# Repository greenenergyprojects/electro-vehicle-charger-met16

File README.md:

# Electrovehicle IEC 62196 Typ 2 charger met-16

## Features:

* Charger Box for electro vehicle 230V/16A -> IEC 62196 Typ 2
* Charge current adjustable between 7A and 16A
* Controlled by Atmel Atmega328P microcontroller (Arduino nano)
* Optional: voltage and current measurement on board
* Optional: LCD connector (2x20 characters, 4 bit mode)

## Newest version ready to use

* [Branch v0.3](https://github.com/greenenergyprojects/electro-vehicle-charger-met16/tree/v0.3)
* PCB: [kicad/dist](kicad/dist)
* Software: [software/atmega328p_u1/ev-charge-control/released](software/atmega328p_u1/ev-charge-control/released)

See README.md files in subfolders for more information.

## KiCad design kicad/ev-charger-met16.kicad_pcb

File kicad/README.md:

# Electrovehicle IEC 62196 Typ 2 charger met-16

## Issues / Test results

Issues can be found in file [dist/README.md](dist/README.md).

## PCB / Kicad project

Design files can be found in the [same directory](./).

## Tapeout / Manufactering data

Manufactering data can be found in subdirectory [dist](dist).

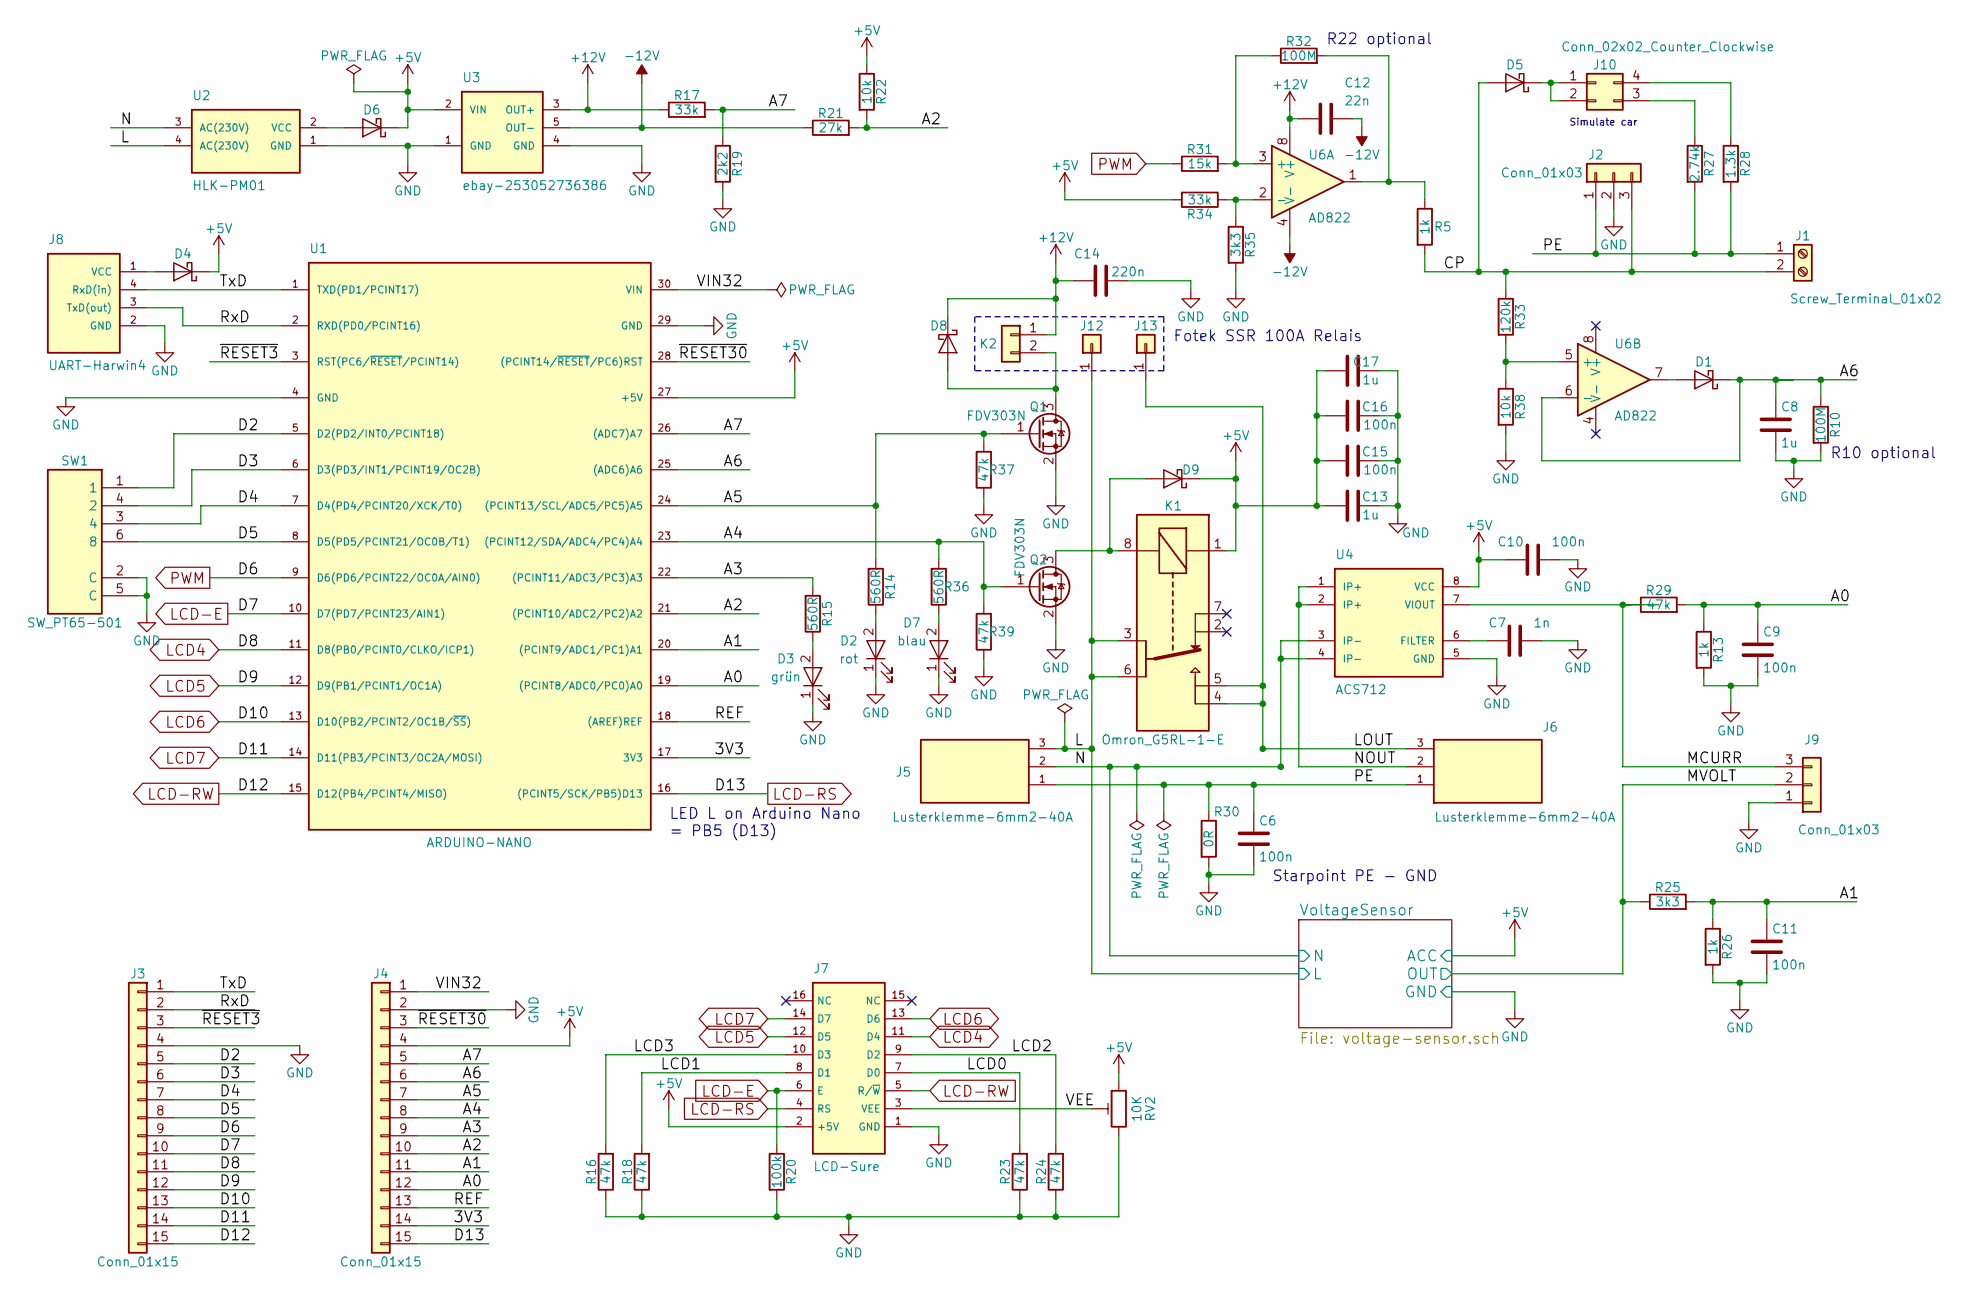
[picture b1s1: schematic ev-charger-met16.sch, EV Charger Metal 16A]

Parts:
C6, C9, C10, C11, C15, C16: 100n; C_1206_HandSoldering
C7: 1n; C_1206_HandSoldering
C8, C13, C17: 1u; C_1206_HandSoldering
C12: 22n; C_1206_HandSoldering
C14: 220n; C_1206_HandSoldering
D1, D4, D5, D8, D9: D_Schottky; D_SMA_Handsoldering
D2: rot; LED_PLCC-2
D3: grün; LED_PLCC-2
D6: D_Schottky; D_SMA-SMB_Universal_Handsoldering
D7: blau; LED_PLCC-2
J1: Screw_Terminal_01x02; Terminalblock-2x-5mm
J2, J9: Conn_01x03; Pin_Header_Straight_1x03_Pitch2.54mm
J3, J4: Conn_01x15; Pin_Header_Straight_1x15_Pitch2.54mm
J5: Lusterklemme-6mm2-40A; Lusterklemme-PA30P-6mm2-40A-x3-N
J6: Lusterklemme-6mm2-40A; Lusterklemme-PA30P-6mm2-40A-x3-S
J7: LCD-Sure; LCD-Sure-shifted-064
J8: UART-Harwin4; Harwin_LTek-Male_04x2.00mm_Straight_StrainRelief
J10: Conn_02x02_Counter_Clockwise; Pin_Header_Straight_2x02_Pitch2.54mm
J12, J13: Conn_01x01; Solder_via_5x5_forWire4mm2
K1: Omron_G5RL-1-E; Relay_DPDT_Panasonic_JW2
K2: Conn_01x02; Pin_Header_Straight_1x02_Pitch2.54mm
Q1, Q2: FDV303N; SOT-23_Handsoldering
R5, R13, R26: 1k; R_1206_HandSoldering
R10, R32: 100M; R_1206_HandSoldering
R14, R15, R36: 560R; R_1206_HandSoldering
R16, R18, R23, R24, R29, R37, R39: 47k; R_1206_HandSoldering
R17, R34: 33k; R_1206_HandSoldering
R19: 2k2; R_1206_HandSoldering
R20: 100k; R_1206_HandSoldering
R21: 27k; R_1206_HandSoldering
R22, R38: 10k; R_1206_HandSoldering
R25, R35: 3k3; R_1206_HandSoldering
R27: 2.74k; R_1206_HandSoldering
R28: 1.3k; R_1206_HandSoldering
R30: 0R; R_1206_HandSoldering
R31: 15k; R_1206_HandSoldering
R33: 120k; R_1206_HandSoldering
RV2: 10K; Potentiometer_Trimmer_Bourns_3296W
SW1: SW_PT65-501; SW_DIP_x3_W7.62mm_PT65-501
U1: ARDUINO-NANO; Arduino-Nano
U2: HLK-PM01; HLK_PM01
U3: ebay-253052736386
U4: ACS712; SO-8_5.3x6.2mm_Pitch1.27mm
U6: AD822; SO-8_5.3x6.2mm_Pitch1.27mm

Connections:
+5V: C10.2, C13.1, C15.1, C16.1, C17.1, D4.1 (K), D6.1 (K), D9.1 (K), J4.4, J7.2 (+5V), K1.1, R22.1, R34.2, RV2.1, U1.27 (+5V), U3.2 (VIN), U4.8 (VCC); also elsewhere on the board
+12V: C12.2, C14.1, D8.1 (K), K2.1, R17.1, U3.3 (OUT+), U6.8 (V+)
-12V: C12.1, R21.1, U3.5 (OUT-), U6.4 (V-)
/3V3: J4.14, U1.17 (3V3)
/A0: C9.1, J4.12, R13.1, R29.2, U1.19 ((PCINT8/ADC0/PC0)A0)
/A1: C11.1, J4.11, R25.2, R26.1, U1.20 ((PCINT9/ADC1/PC1)A1)
/A2: J4.10, R21.2, R22.2, U1.21 ((PCINT10/ADC2/PC2)A2)
/A3: J4.9, R15.2, U1.22 ((PCINT11/ADC3/PC3)A3)
/A4: J4.8, Q2.1 (G), R36.2, R39.2, U1.23 ((PCINT12/SDA/ADC4/PC4)A4)
/A5: J4.7, Q1.1 (G), R14.2, R37.2, U1.24 ((PCINT13/SCL/ADC5/PC5)A5)
/A6: C8.1, D1.1 (K), J4.6, R10.1, U1.25 ((ADC6)A6), U6.6 (-)
/A7: J4.5, R17.2, R19.1, U1.26 ((ADC7)A7)
/CP: D5.2 (A), J1.2, J2.3, R5.2, R33.1
/D2: J3.5, SW1.1, U1.5 (D2(PD2/INT0/PCINT18))
/D3: J3.6, SW1.4 (2), U1.6 (D3(PD3/INT1/PCINT19/OC2B))
/D4: J3.7, SW1.3 (4), U1.7 (D4(PD4/PCINT20/XCK/T0))
/D5: J3.8, SW1.6 (8), U1.8 (D5(PD5/PCINT21/OC0B/T1))
/L: J5.3, J12.1, K1.3, K1.6, U2.4 (AC(230V)); also elsewhere on the board
/LCD0: J7.7 (D0), R23.2
/LCD1: J7.8 (D1), R18.2
/LCD2: J7.9 (D2), R24.2
/LCD3: J7.10 (D3), R16.2
/LOUT: J6.3, J13.1, K1.4, K1.5
/MCURR: J9.3, R29.1, U4.7 (VIOUT)
/MVOLT: J9.2, R25.1; also elsewhere on the board
/N: J5.2, U2.3 (AC(230V)), U4.3 (IP-), U4.4 (IP-); also elsewhere on the board
/NOUT: J6.2, U4.1 (IP+), U4.2 (IP+)
/PE: C6.1, J1.1, J2.1, J5.1, J6.1, R27.2, R28.2, R30.1
/REF: J4.13, U1.18 ((AREF)REF)
/RxD: J3.2, J8.3 (TxD(out)), U1.2 (RXD(PD0/PCINT16))
/TxD: J3.1, J8.4 (RxD(in)), U1.1 (TXD(PD1/PCINT17))
/VEE: J7.3 (VEE), RV2.2
/VIN32: J4.1, U1.30 (VIN)
/~RESET3~: J3.3, U1.3 (RST(PC6/~RESET~/PCINT14))
/~RESET30~: J4.3, U1.28 ((PCINT14/~RESET~/PC6)RST)
GND: C6.2, C7.1, C8.2, C9.2, C10.1, C11.2, C13.2, C14.2, C15.2, C16.2, C17.2, D2.1 (K), D3.1 (K), D7.1 (K), J2.2, J3.4, J4.2, J7.1 (GND), J8.2 (GND), J9.1, Q1.2 (S), Q2.2 (S), R10.2, R13.2, R16.1, R18.1, R19.2, R20.2, R23.1, R24.1, R26.2, R30.2, R35.2, R37.1, R38.2, R39.1, RV2.3, SW1.2 (C), SW1.5 (C), U1.4 (GND), U1.29 (GND), U2.1 (GND), U3.1 (GND), U3.4 (GND), U4.5 (GND); also elsewhere on the board
LCD4: J3.11, J7.11 (D4), U1.11 (D8(PB0/PCINT0/CLKO/ICP1))
LCD5: J3.12, J7.12 (D5), U1.12 (D9(PB1/PCINT1/OC1A))
LCD6: J3.13, J7.13 (D6), U1.13 (D10(PB2/PCINT2/OC1B/~SS~))
LCD7: J3.14, J7.14 (D7), U1.14 (D11(PB3/PCINT3/OC2A/MOSI))
LCD-E: J3.10, J7.6 (E), R20.1, U1.10 (D7(PD7/PCINT23/AIN1))
LCD-RS: J4.15, J7.4 (RS), U1.16 ((PCINT5/SCK/PB5)D13)
LCD-RW: J3.15, J7.5 (R/~W~), U1.15 (D12(PB4/PCINT4/MISO))
unnamed: C7.2, U4.6 (FILTER)
unnamed: D1.2 (A), U6.7
unnamed: D2.2 (A), R14.1
unnamed: D3.2 (A), R15.1
unnamed: D4.2 (A), J8.1 (VCC)
unnamed: D5.1 (K), J10.1, J10.2
unnamed: D6.2 (A), U2.2 (VCC)
unnamed: D7.2 (A), R36.1
unnamed: D8.2 (A), K2.2, Q1.3 (D)
unnamed: D9.2 (A), K1.8, Q2.3 (D)
unnamed: J10.3, R27.1
unnamed: J10.4, R28.1
unnamed: R31.2, R32.1, U6.3 (+)
unnamed: R5.1, R32.2, U6.1
unnamed: R33.2, R38.1, U6.5 (+)
unnamed: R34.1, R35.1, U6.2 (-)
PWM: J3.9, R31.1, U1.9 (D6(PD6/PCINT22/OC0A/AIN0))

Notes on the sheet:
Starpoint PE - GND
Simulate car
R10 optional
R22 optional
LED L on Arduino Nano = PB5 (D13)
Fotek SSR 100A Relais

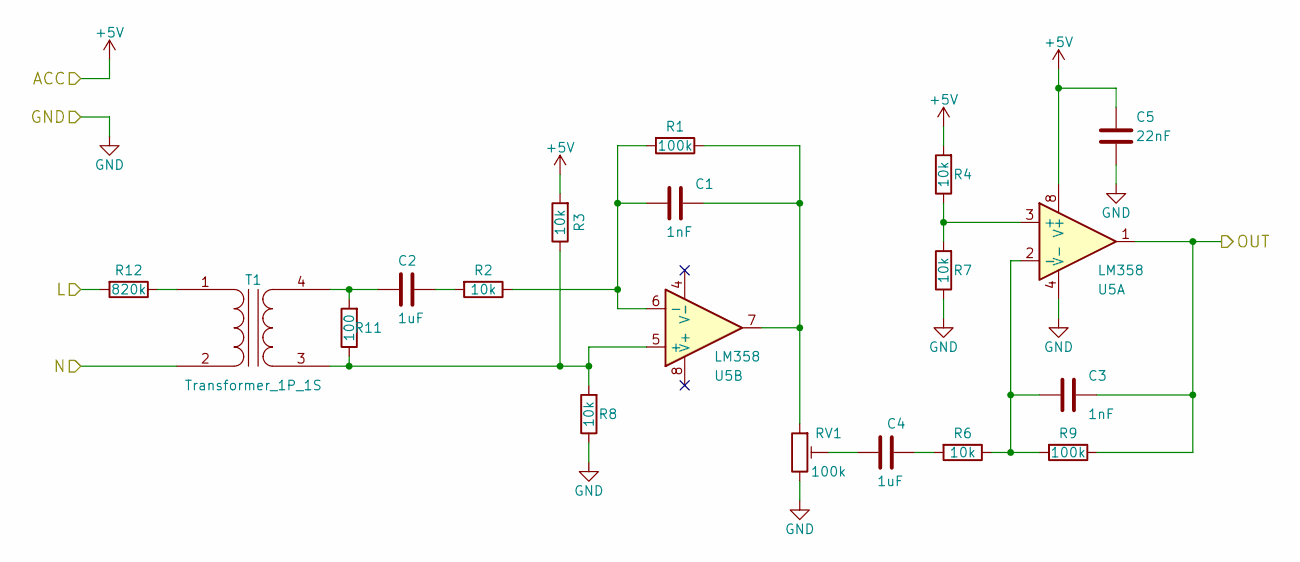
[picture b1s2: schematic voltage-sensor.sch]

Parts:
C1, C3: 1nF; C_1206_HandSoldering
C2, C4: 1uF; C_1206_HandSoldering
C5: 22nF; C_1206_HandSoldering
R1, R9: 100k; R_1206_HandSoldering
R2, R3, R4, R6, R7, R8: 10k; R_1206_HandSoldering
R11: 100; R_1206_HandSoldering
R12: 820k; R_1206_HandSoldering
RV1: 100k; Potentiometer_Trimmer_Bourns_3296W
T1: Transformer_1P_1S; Transformer-zmpt101b_ebay-121438904988
U5: LM358; SO-8_5.3x6.2mm_Pitch1.27mm

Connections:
+5V: C5.1, R3.2, R4.2, U5.8 (V+); also elsewhere on the board
/L: R12.2; also elsewhere on the board
/MVOLT: C3.1, R9.1, U5.1; also elsewhere on the board
/N: T1.2 (AB); also elsewhere on the board
GND: C5.2, R7.1, R8.1, RV1.3, U5.4 (V-); also elsewhere on the board
unnamed: C1.1, R1.1, RV1.1, U5.7
unnamed: C1.2, R1.2, R2.1, U5.6 (-)
unnamed: C2.1, R2.2
unnamed: C2.2, R11.2, T1.4 (SB)
unnamed: C3.2, R6.1, R9.2, U5.2 (-)
unnamed: C4.1, R6.2
unnamed: C4.2, RV1.2
unnamed: R4.1, R7.2, U5.3 (+)
unnamed: R3.1, R8.2, R11.1, T1.3 (SA), U5.5 (+)
unnamed: R12.1, T1.1 (AA)

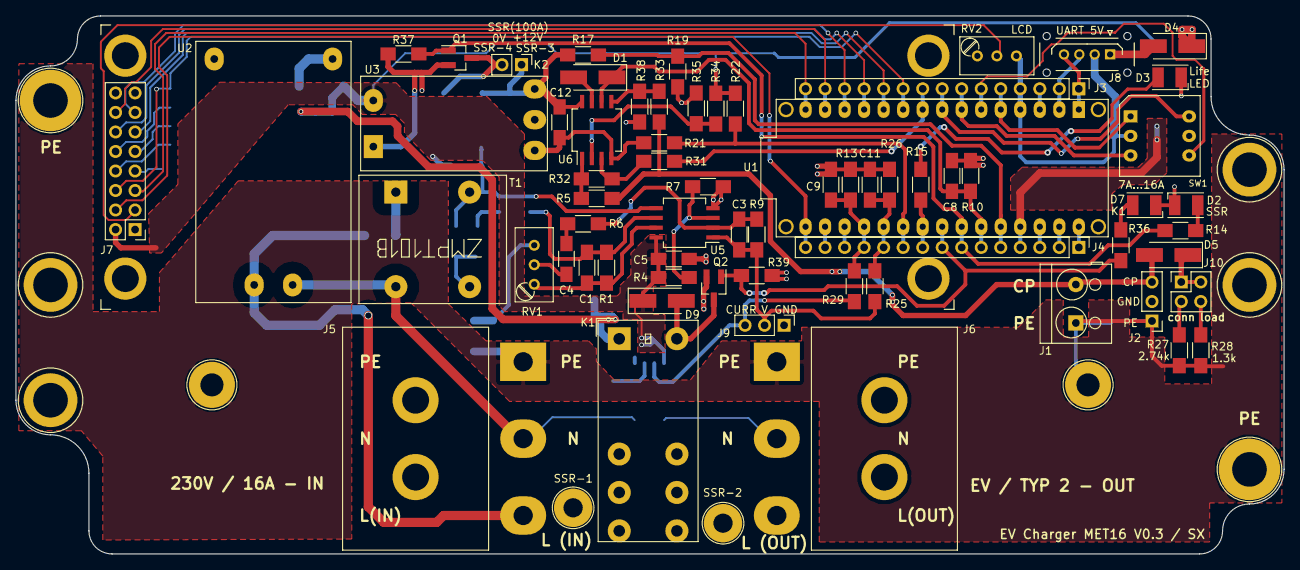
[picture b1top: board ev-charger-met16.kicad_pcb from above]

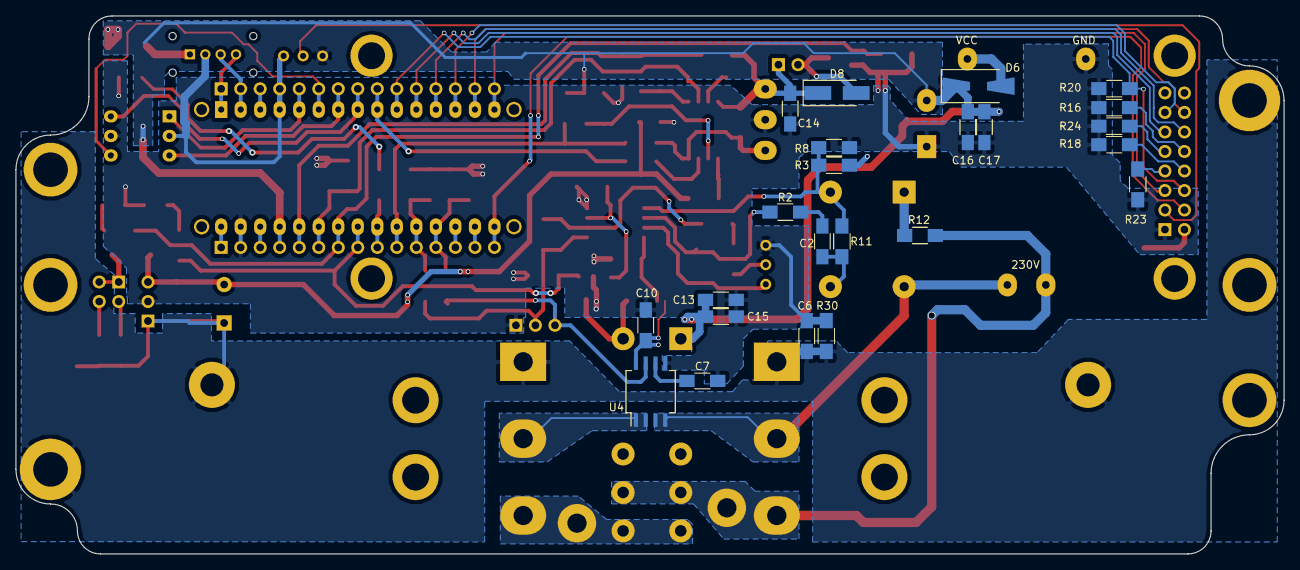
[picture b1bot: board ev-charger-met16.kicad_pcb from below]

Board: 2 copper layers, 165.0 x 70.0 mm, 91 parts (23 on the bottom side), 70 nets.

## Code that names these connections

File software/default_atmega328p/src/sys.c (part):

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  memset((void *)&sys, 0, sizeof(sys));
 _delay_ms(10);

  // Life LED PB5 (Arduino Nano)
  // DDRB |= (1 << PB5); // not available, Port used for LCD
 
  // Timer for state-machine
  OCR2A  = (F_CPU+4)/8/10000-1;
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
#ifdef GLOBAL_LCD  
  PORTB  &= ~0x3f;        // RS, RW, D7, D6, D5, D4
  PORTD  &= ~(1 << PD7);  // E
  DDRB   |=  0x3f;        // RS, RW, D7, D6, D5, D4
  DDRD   |= (1 << PD7);   // E
  sys_lcd_init();
#endif

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  stdin  = &mystdin;
  
  // settings for ev-charger-met
  DDRC |= (1 << PC3); // LED D3 (PC3) - Life LED (green)
  DDRC |= (1 << PC4); // LED D7 - K1 relais (LED blue)
  DDRC |= (1 << PC5); // LED D2 - K2 SSR relais (LED red)
  DDRD &= ~(0x3c); // SW1 (rotary switch 0-9) PD2/PD3/PD4/PD5
  PORTD |= 0x3c;   // pull up on rotary switch
  
  // ADC: ADC0=Current 0A..16A, ADC1=230V Voltage, 
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        TCCR0A = 0;
        TCCR0B = 0;
        OCR0A = 0;
        DDRD |= (1 << PD6);
        PORTD &= ~(1 << PD6);
    }
}

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/*
void sys_setNanoLed (uint8_t ledState) {
    if (ledState)
        PORTB |= (1 << PB5);
    else
        PORTB &= ~(1 << PB5);
}

void sys_toggleNanoLed (void) {
    PORTB ^= (1 << PB5);
}
*/

void sys_setK1 (uint8_t on) {
    DDRC |= (1 << PC4); // PC4 - K1 (Relais 230V/16A)
    if (on) {
        PORTC |= (1 << PC4);
    } else {
        PORTC &= ~(1 << PC4);
    }
}

void sys_setK2 (uint8_t on) {
    DDRC |= (1 << PC5); // PC5 - K2 (Fotek SSR 100A)
    if (on) {
        PORTC |= (1 << PC5);
    } else {
        PORTC &= ~(1 << PC5);
    }
}


void sys_setLedD3 (uint8_t ledState) {
    if (ledState)
        PORTC |= (1 << PC3);
    else
        PORTC &= ~(1 << PC3);
}

void sys_toggleLedD3 (void) {
    PORTC ^= (1 << PC3);
}

/*
void sys_setLedD2 (uint8_t ledState) {
    if (ledState)
        PORTC |= (1<<PC4);
    else
        PORTC &= ~(1 << PC4);
}

void sys_toggleLedD2 (void) {
    PORTC ^= (1 << PC4);
}

int sys_isSw2On () {
    return (PINC & (1 << PC5)) != 0;
}
*/

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
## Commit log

2018-08-02 v0.2, first protoype
2018-08-05 Redesign v0.3 finished, gerber-files ready for print production
2018-08-05 update project settings
2018-09-01 Bugfix Software
2019-10-30 v0.3 manufact. report / software for voltage upper/lower half measurment
2019-11-01 new software atmega328p_u1 based on C++/vscode
2019-11-04 software ready, energy calculation not implemented, not tested
2019-11-05 energy measurement implemented, ready for first EV test
2019-11-11 eeprom logging ready for use
2019-11-11 ev-charge-control V0.3.1~20191111-103422
2019-11-13 Add images from v0.3 manufactured print
2019-11-13 Add image ev-charger-m16.jpg
2019-11-13 Update Software atmega328p_u1/ev-charge-control
2019-11-24 Messung Netzspannung
